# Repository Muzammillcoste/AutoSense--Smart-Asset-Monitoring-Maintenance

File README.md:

# AutoSense — Smart Asset Monitoring & Maintenance

AutoSense is a prototype vehicle-monitoring system built as an undergraduate final-year project at NED University of Engineering & Technology, Karachi. The project report calls it *Smart Asset Tracking and Predictive Maintenance System for Flight Catering*. It connects a custom ESP32-S3 sensor unit, a cloud monitoring dashboard, 24-hour sensor-reading forecasts, and Salesforce alert records into a single maintenance workflow.

This repository holds the prototype source (firmware, PCB, simulators, dashboard widgets, inference script, Salesforce Apex). It also holds a later re-evaluation of the forecasting models, published as a preprint on Zenodo ([DOI 10.5281/zenodo.22665260](https://doi.org/10.5281/zenodo.22665260)).

> **Scope in one sentence:** AutoSense forecasts future sensor readings (engine temperature, tyre pressure, tyre temperature) and compares readings and forecasts against fixed thresholds. It does **not** predict component failures or estimate remaining useful life, and it has not been evaluated on recorded fleet data.

## Prototype scope at a glance

| | What it covers | Evidence |
|---|---|---|
| **Physically built** | ESP32-S3 unit with NEO-6M GPS, one DS18B20 temperature probe and four BLE tyre-pressure (TPMS) sensors, mounted on one test vehicle. Custom PCB designed in KiCad. | Firmware, KiCad project, BOM; mounting reported by the team ([`Real Sensors.txt`](Real%20Sensors.txt)) |
| **Simulated** | Additional vehicles (random-walk readings for 4–5 vehicles) and all ML training data (synthetic 2024 time series) | [`Simulator/`](Simulator/), [`IoT/simulator/`](IoT/simulator/), generator notebooks |
| **Integrated** | Sensor unit → Swift platform (Ephlux) → dashboard; threshold alerts → Salesforce `Vehicle_Alert__c` records; Salesforce status change → Swift via Apex trigger; batch forecasts → Swift | Source code and interface screenshots below |
| **Evaluated** | Offline forecast accuracy on synthetic data and on the public NASA C-MAPSS FD001 simulator benchmark. No evaluation of maintenance outcomes. | [`research_v2/`](research_v2/) saved results |

## Screenshots

Fleet map, live alerts and per-sensor view on the Swift dashboard. The readings shown come from the prototype unit and the simulators:

An alert record created in Salesforce from a Swift alert:

PCB layout (KiCad 3D render; the CAN-bus and fuel-sensor headers were not used by the firmware):

There is also a project explainer video at [`Graphics/Explainer Video.mp4`](Graphics/Explainer%20Video.mp4), along with a [poster](Graphics/Poster.pdf) and a [brochure](Graphics/Brochure(1).pdf).

## Problem and intended users

AutoSense was designed for maintenance and fleet teams managing ground-support vehicles in flight-catering operations. The project explored how live condition monitoring and forecast-based alerts could supplement reactive or fixed-schedule maintenance. The project set out to give them live location and condition data, early warnings from forecasts, and a ticket-like record in Salesforce for each alert.

The project was reviewed with the team's industry advisor at Ephlux. The main feedback recorded was that the dashboard should be more intuitive. Claims in the project report about reduced downtime or maintenance cost were stated goals. They were never measured.

## Team and contributions

Final-year project, Department of Computer & Information Systems Engineering, NED University of Engineering & Technology (batch 2021–2025). Supervised by Dr. Shahab Tehzeeb, with industry advisor Nadeem Ali (Ephlux).

The table follows the signed *Statement of Contributions* in the [final report](Documents/3_Final-Report.pdf).

| Member | Contributions (from the final report) |
|---|---|
| **Muzammil Rizvi** | Sensor-data integration into the database; webhooks for real-time updates; Salesforce integration and Swift ↔ Salesforce sync; ticket and alert generation logic; ML model R&D, training and deployment |
| Wahaj Raza | Real-time dashboard graphs; alerts and notification system in Swift; ML model R&D and training; deployment-ready model pipeline; database schema; middleware–DB–frontend integration |
| Huzaifa Naseer Khan | ESP32 firmware; sensor integration and hardware assembly; Google Maps integration; readings and alerts tables; mock sensor-data simulation |
| Farrukh Niaz | Sensor and ML research; alerts widget; data-forwarding checks; view and entry forms; input validation; flow diagrams; documentation |

**Post-project re-evaluation (2026).** Muzammil Rizvi audited the original ML results and rebuilt the evaluation protocol in [`research_v2/`](research_v2/). This covered the corrected benchmark, multi-seed and ablation runs, C-MAPSS external evaluation, and preparation of the manuscript. All four team members are co-authors of the resulting preprint.

**Repository history.** The project-era commits (April–June 2025) were made in [HuzaifaNaseer02/AutoSense---Smart-Asset-Monitoring-Maintenance](https://github.com/HuzaifaNaseer02/AutoSense---Smart-Asset-Monitoring-Maintenance) and merged here. This repository is the maintained copy and includes the 2026 re-evaluation.

## System architecture and data flow

```mermaid
flowchart LR
    S["Sensors<br/>GPS · DS18B20 · 4× BLE TPMS"] --> E["ESP32-S3 firmware<br/>JSON over HTTPS"]
    SIM["Simulators<br/>(Node.js / ESP32)"] --> SW
    E -->|readings every 5 s<br/>GPS every 2 s| SW["Swift platform (Ephlux)<br/>storage · workflows · dashboard"]
    E -->|fixed-threshold alerts| SW
    SW -->|sensor history| P["Batch forecaster<br/>main.py · 3 Keras models"]
    P -->|24 h forecasts| SW
    SW -->|alerts, vehicles| SF["Salesforce<br/>Vehicle__c · Vehicle_Alert__c"]
    SF -->|status change<br/>Apex trigger| SW
```

There are two separate alert paths:

1. **Reading-based alerts** run on the device. The firmware compares each reading with fixed limits: tyre pressure > 32 or ≤ 25 PSI, probe temperature ≥ 80 °C.
2. **Forecast-based alerts** run in the dashboard widget [`PredictedVehicleAlerts.js`](Custom%20Components/In%20Prod/PredictedVehicleAlerts.js). It applies a different set of fixed limits (engine > 95 °C, tyre temperature > 70 °C, pressure < 28 PSI) to the model forecasts.

In both paths the alert itself comes from a threshold rule. The ML models only produce the forecast values that the second rule checks.

## Implemented components

| Folder | Contents | Notes |
|---|---|---|
| [`IoT/hardware/FINAL_ESP32_FIRMWARE/`](IoT/hardware/FINAL_ESP32_FIRMWARE/) | Final Arduino firmware: Wi-Fi with NTP time, GPS over UART, DS18B20 over OneWire, BLE TPMS decoding by MAC address, HTTP POST of readings and alerts | Other sketches in `IoT/hardware/` are earlier single-sensor tests |
| [`IoT/PCB/`](IoT/PCB/) | KiCad schematic and layout, STEP model, production files (BOM, positions, netlist) | See also [`IoT/PCB Schematic.pdf`](IoT/PCB%20Schematic.pdf) |
| [`Simulator/`](Simulator/), [`IoT/simulator/`](IoT/simulator/) | Node.js and ESP32 simulators that post random-walk readings and alerts for 4–5 vehicles | Used for multi-vehicle demos and testing |
| [`Custom Components/In Prod/`](Custom%20Components/In%20Prod/) | Five React widget bodies for the Swift dashboard: map, live sensor charts, status and alert charts, forecast charts, forecast alerts | Written for Swift's component editor. They have no imports and can't run on their own. |
| [`Models and scripts/`](Models%20and%20scripts/) | `main.py` batch pipeline: fetch readings from Swift → feature engineering → three Keras models → post forecasts to Swift. Includes the deployed models and scalers. | Prototype script, see limitations |
| [`FYP ML Training and Pipeline Code/`](FYP%20ML%20Training%20and%20Pipeline%20Code/) | Original data-generation, training and testing notebooks for the three models | Superseded as evaluation evidence by `research_v2/` |
| [`Salesforce/`](Salesforce/) | Salesforce DX project with three Apex classes (pull alerts and vehicles from Swift, push status back) and a `Vehicle__c` trigger | The custom-object metadata isn't in the repository |
| [`research_v2/`](research_v2/) | Corrected forecasting benchmark, audit of the original results, extended experiments, paper sources | Manuscript PDF: [`research_v2/paper/build/main.pdf`](research_v2/paper/build/main.pdf). See below |
| [`Documents/`](Documents/) | Proposal, final report, original paper draft, presentations | Some ML figures in these documents are superseded (see below) |

## Data sources and simulation

- **Training data is synthetic.** The three training series (Karachi engine temperature, hourly; tyre pressure and tyre temperature, 3-hourly; calendar year 2024) come from generator notebooks in this repository. [`research_v2/verify_generators.py`](research_v2/verify_generators.py) reproduces every timestamp and value of the committed CSVs. The files in [`Dataset/`](Dataset/) are also generated.
- **Live readings** came from the prototype unit and the simulators through Swift. They weren't kept as a dataset, so no model was trained or tested on recorded vehicle data.
- **External benchmark:** NASA C-MAPSS FD001, a public, simulator-generated turbofan-degradation dataset. It is used only to test the same forecasting setup on independent data. It is not vehicle data.

## ML methods and evaluation

**Task.** Multi-step forecasting of a single sensor's future values from its own history. Engine temperature uses 168 hourly inputs to forecast 24 hourly outputs; the tyre series use 56 three-hourly inputs to forecast 8 outputs. Both cover seven days of history and a 24-hour horizon. Models compared: persistence (last value), seasonal naive (same time yesterday), Random Forest, and a stacked Bi-LSTM (128/64/32 units).

**Protocol** ([`research_v2/protocol.py`](research_v2/protocol.py)):

- Chronological split of raw rows: 68% train, 12% validation, 20% test.
- A window is kept only if its whole target horizon lies inside one partition.
- Min-max scaling is fitted on training rows only.
- Training runs without shuffling, with early stopping on validation loss.
- Hyperparameters were not selected on test scores.

**Benchmark versus deployed prototype.** The results below describe the corrected offline evaluation in `research_v2/`. The integrated prototype uses the original 11-feature models stored in [`Models and scripts/model_scaler/`](Models%20and%20scripts/model_scaler/); those deployed models are not the re-trained benchmark models. These results therefore do not measure the forecasting performance of the deployed prototype.

**Test-set MAE, synthetic data, seed 42** (from [`research_v2/results/final_comparison.csv`](research_v2/results/final_comparison.csv)):

| Target | Persistence | Seasonal naive | Random Forest | Bi-LSTM |
|---|---:|---:|---:|---:|
| Engine temperature (°C) | 10.16 | 2.62 | **1.71** | 6.20 |
| Tyre pressure (PSI) | **0.56** | 0.78 | 0.74 | 1.18 |
| Tyre temperature (°C) | 5.79 | 3.90 | **2.90** | 6.45 |

**Main finding.** In this setting, simple baselines outperform the Bi-LSTM on all three targets. Across five training seeds, the Bi-LSTM test MAE was:

| Target | Mean test MAE ± standard deviation across seeds |
|---|---:|
| Engine temperature | 5.18 ± 0.66 °C |
| Tyre pressure | 1.26 ± 0.22 PSI |
| Tyre temperature | 5.73 ± 0.89 °C |

These statistics describe variation across training seeds, not confidence intervals for real-world performance. See the [multi-seed summary](research_v2/ieee_results/multiseed_summary.csv).

The Bi-LSTM also failed in the threshold-event test. Forecasts were scored against training-derived proxy thresholds, not real fault labels:

- On engine temperature and tyre pressure, it never predicted a threshold crossing (F1 = 0).
- On tyre temperature, it predicted a crossing for every window (false-positive rate 1.0).

Further experiments (architecture and feature ablations, block-bootstrap intervals, C-MAPSS forecasting and stage analysis) are documented in [`research_v2/EXTENDED_EXPERIMENTS.md`](research_v2/EXTENDED_EXPERIMENTS.md). The C-MAPSS work forecasts sensor readings only and does not estimate remaining useful life.

**Evaluation update.** The original project report and paper draft contain metrics that were superseded by the 2026 audit. Use the corrected benchmark results above when citing this work. The [evaluation audit](research_v2/AUDIT.md) documents the original reporting issues, their reconstruction and the revised protocol.

**Important caveats.**

- All AutoSense metrics come from synthetic series, and the test windows overlap, so their errors are not independent.

## Setup and demonstration

This is a collection of components, not a single application you can run with one command. Running the full pipeline needs access to the team's Swift workspace (an Ephlux platform), which isn't public. The code references the team's Swift workspace. To reproduce the integration, configure endpoints and credentials for a workspace you control.

**Firmware** ([`FINAL_ESP32_FIRMWARE.ino`](IoT/hardware/FINAL_ESP32_FIRMWARE/FINAL_ESP32_FIRMWARE.ino))

- Hardware: ESP32-S3-DevKitC-1, NEO-6M GPS on UART2 (RX 16 / TX 17, 9600 baud), DS18B20, and BLE TPMS sensors.
- Libraries: ESP32 Arduino core (WiFi, HTTPClient, BLE), OneWire, DallasTemperature, ArduinoJson, TinyGPS++.
- Before flashing, fill in the Wi-Fi credentials, Swift webhook keys and your own TPMS MAC addresses.

**Simulator**

```sh
cd Simulator
npm install axios
node all_four_simulator.js   # after replacing the YOUR_SWIFT_KEY_* placeholders
```

**Batch forecaster** ([`Models and scripts/main.py`](Models%20and%20scripts/main.py))

```sh
pip install -r "Models and scripts/requirements.txt"
```

Before running it:

- Set the `SWIFT_KEY_VEHICLES`, `SWIFT_KEY_SENSOR_READINGS`, `SWIFT_KEY_DELETE_PREDICTIONS` and `SWIFT_KEY_POST_PREDICTIONS` environment variables.
- Change the hard-coded `/root/FYP-Python-Script/model_scaler/` paths to point at `Models and scripts/model_scaler/`.

The script **deletes and replaces the forecasts stored in Swift**, so only run it against a workspace you control.

**Salesforce** ([`Salesforce/`](Salesforce/)). The Apex code expects these items, which you need to create before deploying (for example with `sf project deploy start`):

- custom objects `Vehicle__c` and `Vehicle_Alert__c` with the fields referenced in the classes
- a Remote Site Setting for the Swift host
- a way to schedule `AlertWebhookService.fetchAndStoreAlerts()` and `VehicleWebhookService.fetchAndStoreVehicles()`

**Forecasting benchmark** ([`research_v2/README.md`](research_v2/README.md)). Requires Python 3.11 and [`research_v2/requirements.txt`](research_v2/requirements.txt). Run from the repository root:

```sh
python -m unittest discover -s research_v2 -p test_protocol.py -v   # protocol tests
python research_v2/verify_generators.py                              # regenerate synthetic data and compare
python research_v2/bilstm_evaluation.py                              # full retrain; overwrites research_v2/results/
```

Full retraining runs on the CPU and takes a long time. The saved outputs in `research_v2/results/` and `research_v2/ieee_results/` can be inspected without rerunning anything.

## Citation

> M. Rizvi, W. Raza, H. Naseer, and F. Niaz, “Benchmarking Multi-Step Sensor Forecasting for Threshold-Based Predictive Maintenance: An Integrated IoT-to-Enterprise Framework,” preprint, Zenodo, 2026. doi:[10.5281/zenodo.22665260](https://doi.org/10.5281/zenodo.22665260)

## Acknowledgements

- Dr. Shahab Tehzeeb (project supervisor, NED University).
- Nadeem Ali and the team at Ephlux, for industry guidance and access to the Swift platform.
- The ESP32-S3 KiCad symbol and footprint in [`IoT/PCB/ESP32_S3_DEVKITC_1_N8R2 (1)/`](IoT/PCB/ESP32_S3_DEVKITC_1_N8R2%20(1)/) are third-party library files under their own [license](IoT/PCB/ESP32_S3_DEVKITC_1_N8R2%20(1)/License.txt).
- NASA C-MAPSS data: Saxena & Goebel (2008).

## License

The code is released under the MIT License. The preprint on Zenodo is licensed separately under CC BY 4.0.

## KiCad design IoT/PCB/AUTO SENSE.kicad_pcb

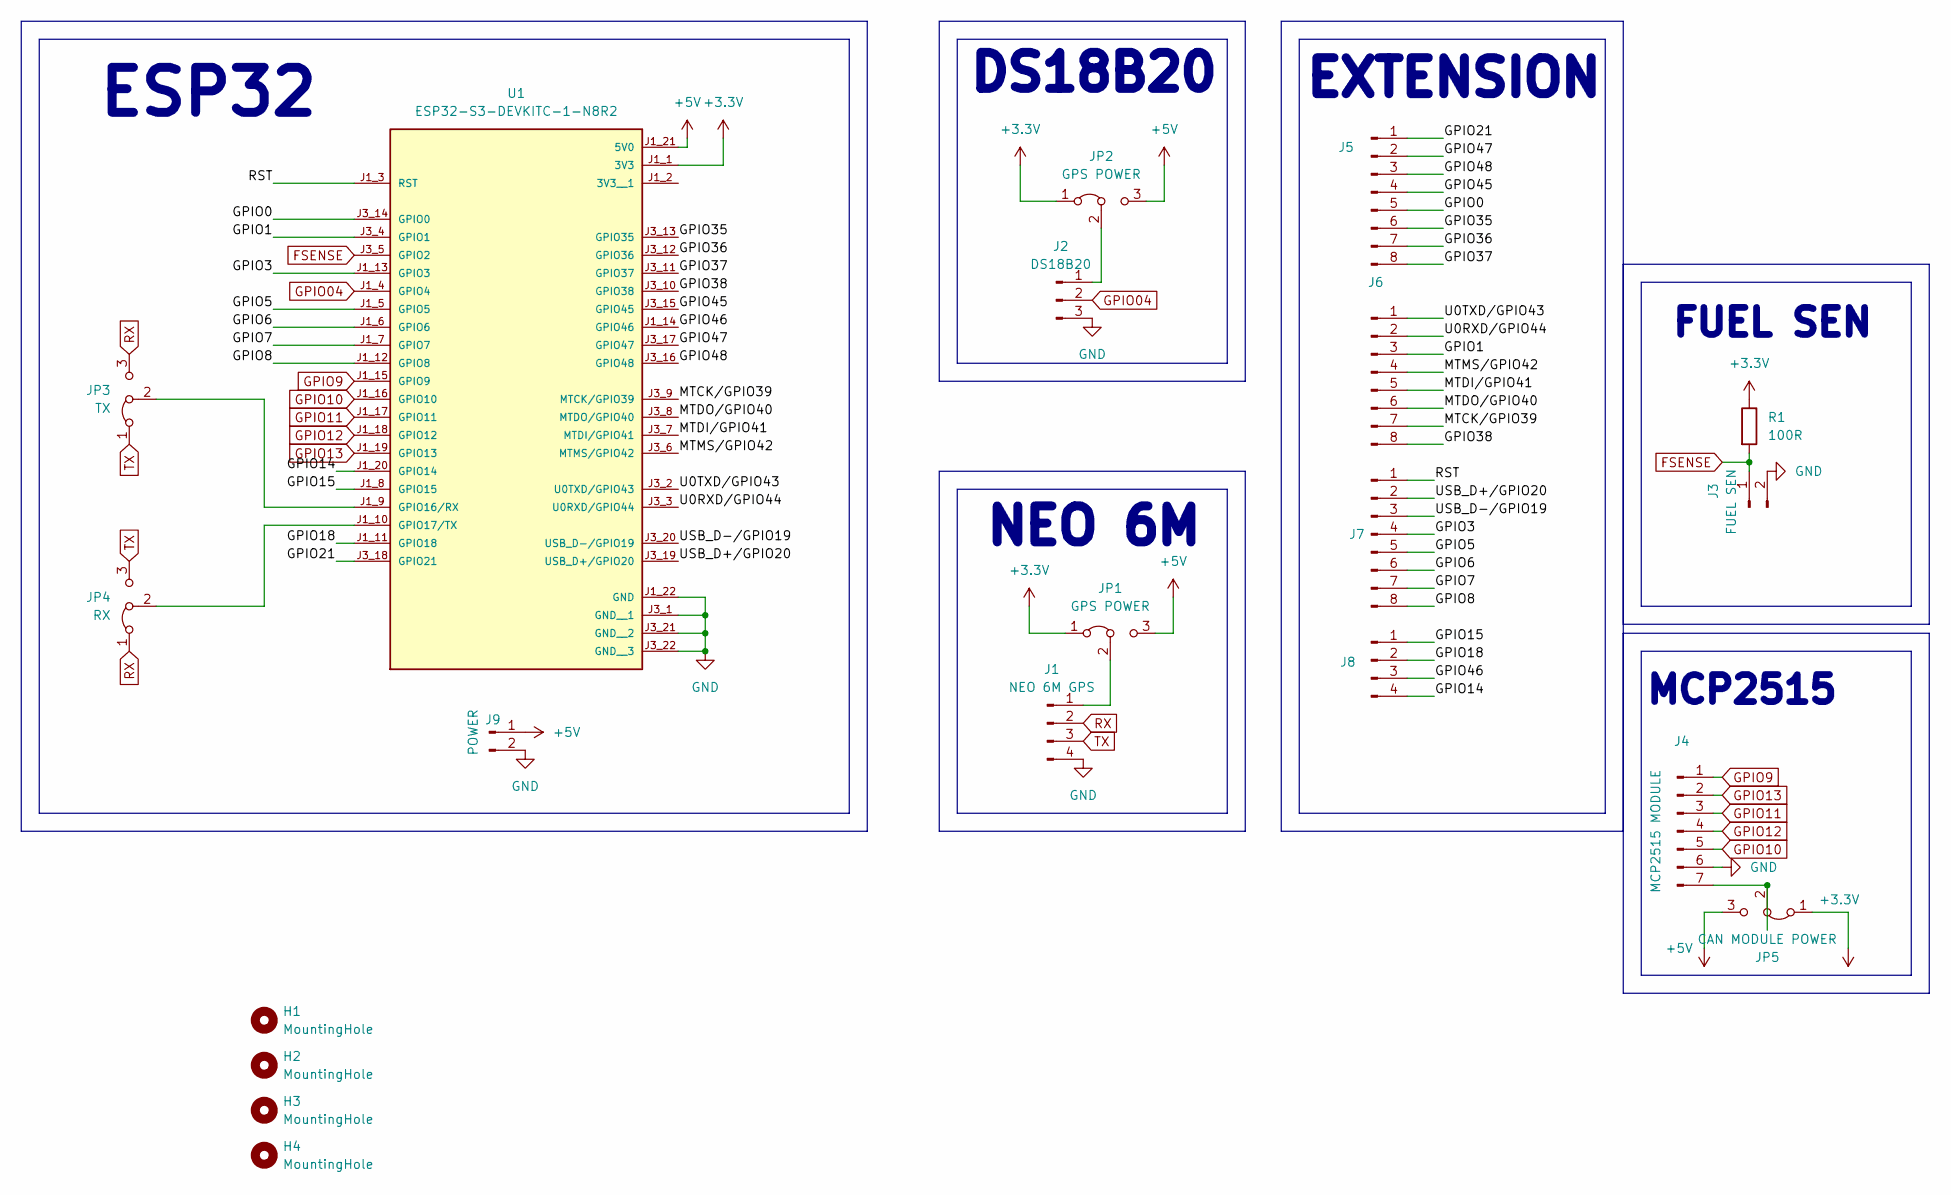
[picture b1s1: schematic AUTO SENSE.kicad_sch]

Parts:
H1, H2, H3, H4: MountingHole; MountingHole_3.2mm_M3
J1: NEO 6M GPS; PinSocket_1x04_P2.54mm_Vertical
J2: DS18B20; TerminalBlock_Phoenix_MKDS-1,5-3-5.08_1x03_P5.08mm_Horizont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
J3: FUEL SEN; TerminalBlock_Phoenix_MKDS-1,5-2-5.08_1x02_P5.08mm_Horizont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
J4: MCP2515 MODULE; PinSocket_1x07_P2.54mm_Horizontal
J5, J6, J7: Conn_01x08_Pin; TerminalBlock_Phoenix_MKDS-1,5-8-5.08_1x08_P5.08mm_Horizont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
J8: CONN; TerminalBlock_Phoenix_MKDS-1,5-4-5.08_1x04_P5.08mm_Horizont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
J9: POWER; TerminalBlock_Phoenix_MKDS-1,5-2-5.08_1x02_P5.08mm_Horizont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
JP1, JP2: GPS POWER; SolderJumper-3_P1.3mm_Bridged2Bar12_RoundedPad1.0x1.5mm
JP3: TX; SolderJumper-3_P1.3mm_Bridged2Bar12_RoundedPad1.0x1.5mm
JP4: RX; SolderJumper-3_P1.3mm_Bridged2Bar12_RoundedPad1.0x1.5mm
JP5: CAN MODULE POWER; SolderJumper-3_P1.3mm_Bridged2Bar12_RoundedPad1.0x1.5mm
R1: 100R; R_Axial_DIN0207_L6.3mm_D2.5mm_P10.16mm_Horizontal
U1: ESP32-S3-DEVKITC-1-N8R2; XCVR_ESP32-S3-DEVKITC-1-N8R2; PARTREV V1

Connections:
+3.3V: JP1.1 (A), JP2.1 (A), JP5.1 (A), R1.1, U1.J1_1 (3V3)
+5V: J9.1, JP1.3 (B), JP2.3 (B), JP5.3 (B), U1.J1_21 (5V0)
/GPIO0: J5.5, U1.J3_14 (GPIO0)
/GPIO1: J6.3, U1.J3_4 (GPIO1)
/GPIO3: J7.4, U1.J1_13 (GPIO3)
/GPIO5: J7.5, U1.J1_5 (GPIO5)
/GPIO6: J7.6, U1.J1_6 (GPIO6)
/GPIO7: J7.7, U1.J1_7 (GPIO7)
/GPIO8: J7.8, U1.J1_12 (GPIO8)
/GPIO14: J8.4, U1.J1_20 (GPIO14)
/GPIO15: J8.1, U1.J1_8 (GPIO15)
/GPIO18: J8.2, U1.J1_11 (GPIO18)
/GPIO21: J5.1, U1.J3_18 (GPIO21)
/GPIO35: J5.6, U1.J3_13 (GPIO35)
/GPIO36: J5.7, U1.J3_12 (GPIO36)
/GPIO37: J5.8, U1.J3_11 (GPIO37)
/GPIO38: J6.8, U1.J3_10 (GPIO38)
/GPIO45: J5.4, U1.J3_15 (GPIO45)
/GPIO46: J8.3, U1.J1_14 (GPIO46)
/GPIO47: J5.2, U1.J3_17 (GPIO47)
/GPIO48: J5.3, U1.J3_16 (GPIO48)
/MTCK/GPIO39: J6.7, U1.J3_9 (MTCK/GPIO39)
/MTDI/GPIO41: J6.5, U1.J3_7 (MTDI/GPIO41)
/MTDO/GPIO40: J6.6, U1.J3_8 (MTDO/GPIO40)
/MTMS/GPIO42: J6.4, U1.J3_6 (MTMS/GPIO42)
/RST: J7.1, U1.J1_3 (RST)
/U0RXD/GPIO44: J6.2, U1.J3_3 (U0RXD/GPIO44)
/U0TXD/GPIO43: J6.1, U1.J3_2 (U0TXD/GPIO43)
/USB_D+/GPIO20: J7.2, U1.J3_19 (USB_D+/GPIO20)
/USB_D-/GPIO19: J7.3, U1.J3_20 (USB_D-/GPIO19)
FSENSE: J3.1, R1.2, U1.J3_5 (GPIO2)
GND: J1.4, J2.3, J3.2, J4.6, J9.2, U1.J1_22 (GND), U1.J3_1 (GND__1), U1.J3_21 (GND__2), U1.J3_22 (GND__3)
GPIO04: J2.2, U1.J1_4 (GPIO4)
GPIO9: J4.1, U1.J1_15 (GPIO9)
GPIO10: J4.5, U1.J1_16 (GPIO10)
GPIO11: J4.3, U1.J1_17 (GPIO11)
GPIO12: J4.4, U1.J1_18 (GPIO12)
GPIO13: J4.2, U1.J1_19 (GPIO13)
unnamed: J1.1, JP1.2 (C)
unnamed: J2.1, JP2.2 (C)
unnamed: J4.7, JP5.2 (C)
unnamed: JP3.2 (C), U1.J1_9 (GPIO16/RX)
unnamed: JP4.2 (C), U1.J1_10 (GPIO17/TX)
RX: J1.2, JP3.3 (B), JP4.1 (A)
TX: J1.3, JP3.1 (A), JP4.3 (B)

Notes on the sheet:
FUEL SEN
EXTENSION
ESP32
MCP2515
NEO 6M
DS18B20

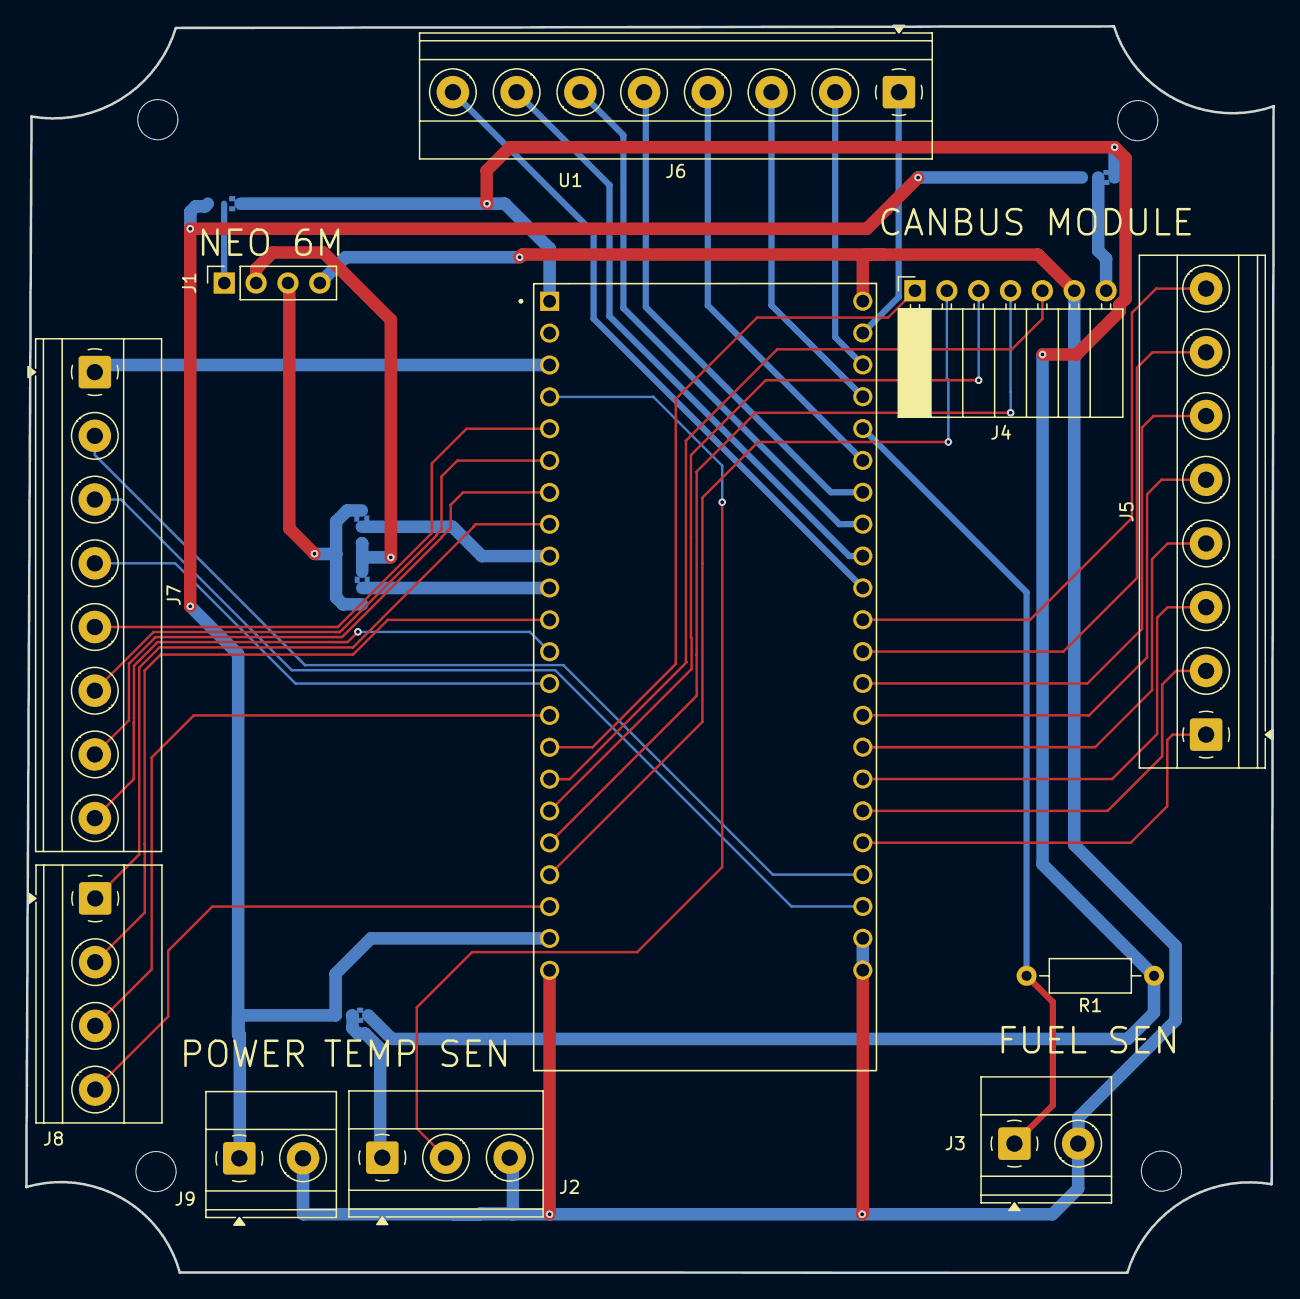
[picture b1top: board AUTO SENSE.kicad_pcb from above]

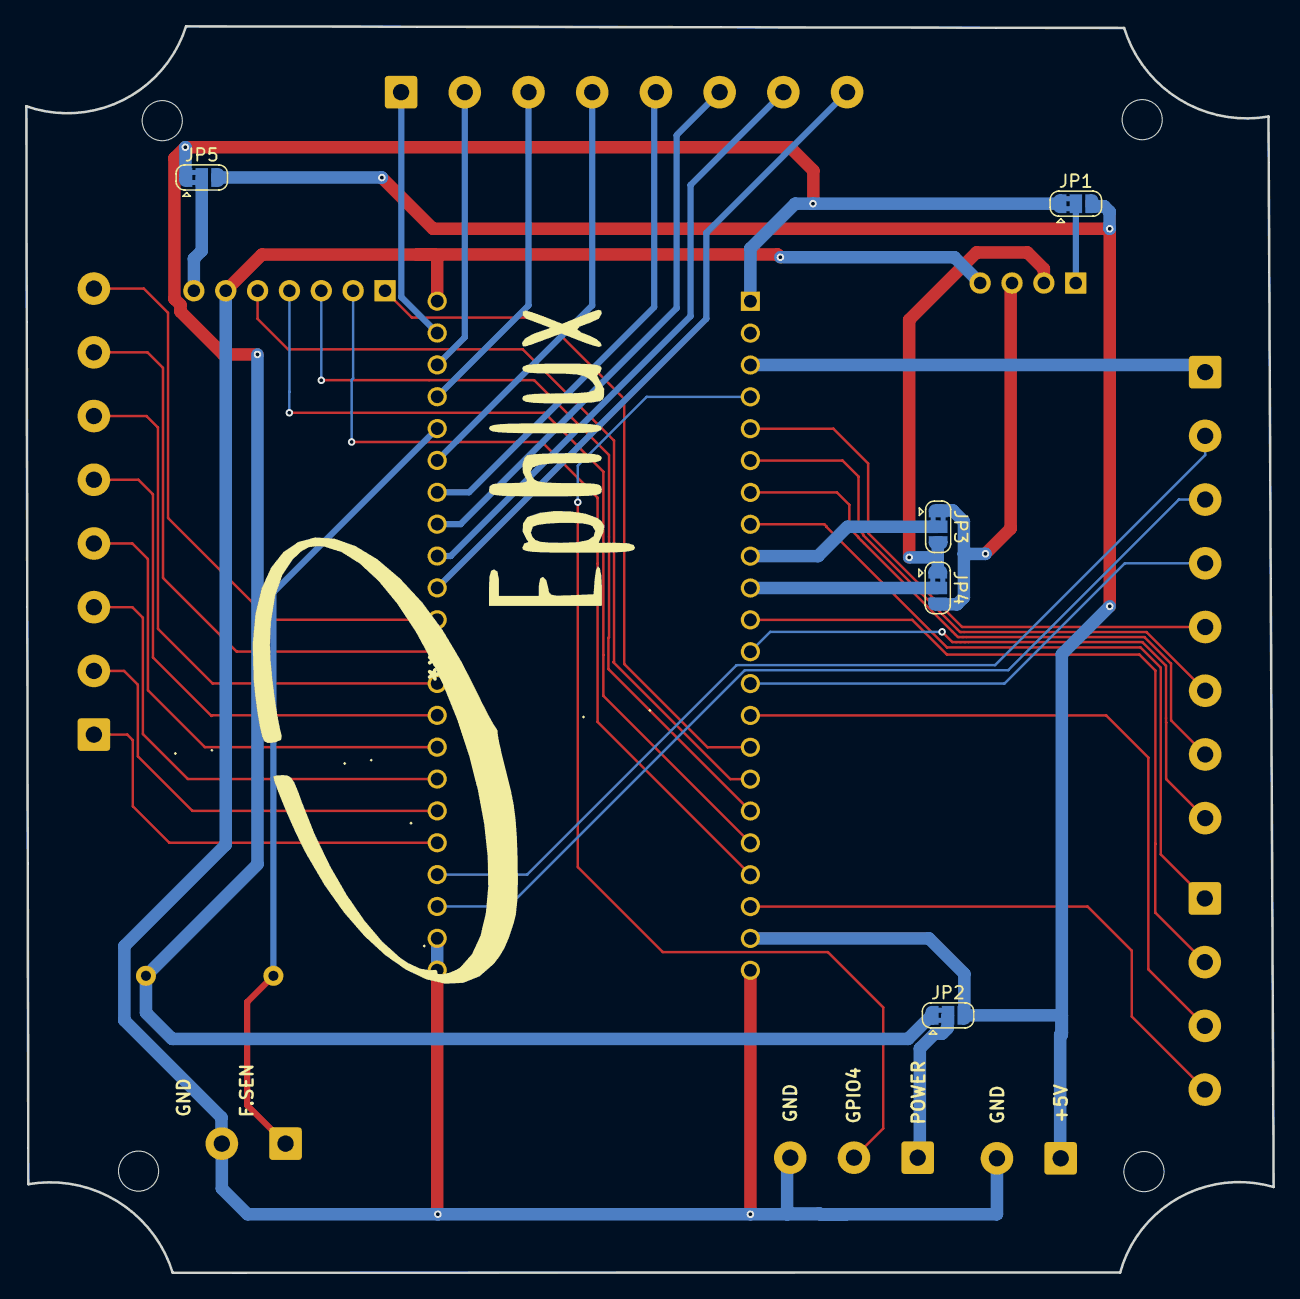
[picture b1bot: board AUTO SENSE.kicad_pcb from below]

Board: 2 copper layers, 99.4 x 99.4 mm, 20 parts (5 on the bottom side), 45 nets.

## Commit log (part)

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2025-04-10 First
2025-04-10 selected
2025-04-12 added tyre temp
2025-04-12 Map move freely
2025-04-12 Added gps
2025-04-13 IoT changes
2025-04-18 ALmost done
2025-04-18 Added graphics
2025-04-18 Add subproject for Python script
2025-04-18 Revert "Add subproject for Python script"
    This reverts commit 83e6eb1d3c94487c67a9e8ce5bd23c2403d9824a.
2025-04-18 Add main script and model files for vehicle temperature and pressure prediction
2025-04-20 Synced app components
2025-05-24 ML Code
2025-05-30 Synced
2025-06-10 Bug fixes
2025-06-10 Fixes
2025-06-10 Add initial Salesforce project structure and services for vehicle alerts and status updates
2025-06-10 Added PCB
2025-06-11 Update README.md with detailed project description and features
2025-06-11 Added docs

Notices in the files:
README.md:
License:
The code is released under the MIT License. The preprint on Zenodo is licensed separately under CC BY 4.0.
